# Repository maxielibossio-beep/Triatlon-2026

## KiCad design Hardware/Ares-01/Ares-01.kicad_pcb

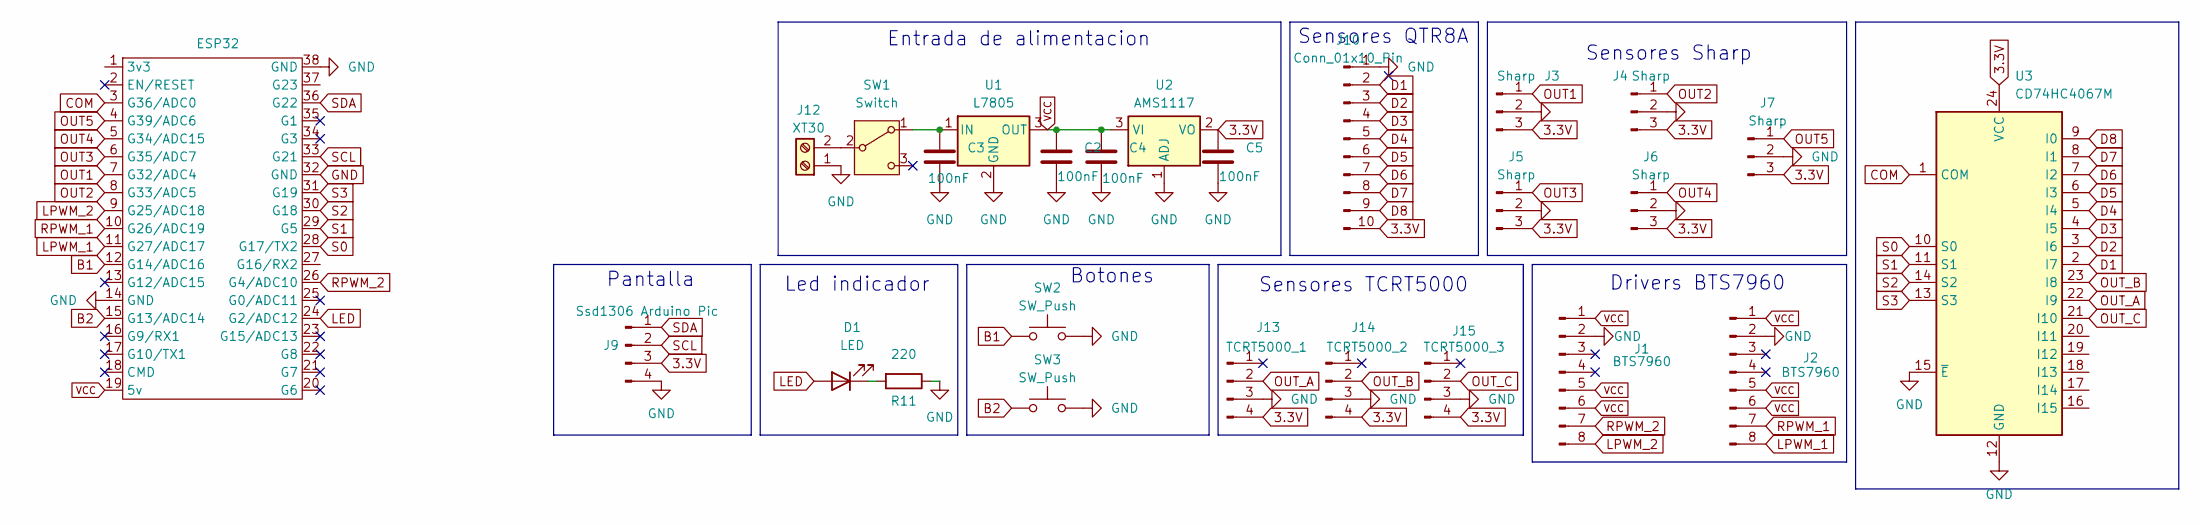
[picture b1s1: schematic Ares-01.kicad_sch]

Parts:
C2, C3, C4, C5: 100nF; C_0805_2012Metric
D1: LED; JST_EH_B2B-EH-A_1x02_P2.50mm_Vertical
ESP32: Nodemcu_ESP32S_38pin
J1, J2: BTS7960; IDC-Header_2x04_P2.54mm_Vertical
J3, J4, J5, J6, J7: Sharp; JST_XH_B3B-XH-A_1x03_P2.50mm_Vertical
J9: Ssd1306 Arduino Pic; JST_XH_B4B-XH-A_1x04_P2.50mm_Vertical
J10: Conn_01x10_Pin; JST_XH_B10B-XH-A_1x10_P2.50mm_Vertical
J12: XT30; XT30 connector
J13: TCRT5000_1; JST_XH_B4B-XH-A_1x04_P2.50mm_Vertical
J14: TCRT5000_2; JST_XH_B4B-XH-A_1x04_P2.50mm_Vertical
J15: TCRT5000_3; JST_XH_B4B-XH-A_1x04_P2.50mm_Vertical
R11: 220; R_0805_2012Metric
SW1: Switch; SW_SPDT_TH_Vertical
SW2, SW3: SW_Push; PUSH_SWITCH_THT
U1: L7805; TO-263-3_TabPin2
U2: AMS1117; SOT-223-3_TabPin2
U3: CD74HC4067M; CD74HC4067_module

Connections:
3.3V: C5.1, J3.3, J4.3, J5.3, J6.3, J7.3, J9.3, J10.10, J13.4, J14.4, J15.4, U2.2 (VO), U3.24 (VCC)
B1: ESP32.12 (G14/ADC16), SW2.1
B2: ESP32.15 (G13/ADC14), SW3.1
COM: ESP32.3 (G36/ADC0), U3.1 (COM)
D1: J10.2, U3.2 (I7)
D2: J10.3, U3.3 (I6)
D3: J10.4, U3.4 (I5)
D4: J10.5, U3.5 (I4)
D5: J10.6, U3.6 (I3)
D6: J10.7, U3.7 (I2)
D7: J10.8, U3.8 (I1)
D8: J10.9, U3.9 (I0)
GND: C2.2, C3.2, C4.2, C5.2, ESP32.14 (GND), ESP32.32 (GND), ESP32.38 (GND), J1.2, J2.2, J3.2, J4.2, J5.2, J6.2, J7.2, J9.4, J10.1, J12.1, J13.3, J14.3, J15.3, R11.1, SW2.2, SW3.2, U1.2 (GND), U2.1 (ADJ), U3.12 (GND), U3.15 (~E)
LED: D1.2 (A), ESP32.24 (G2/ADC12)
LPWM_1: ESP32.11 (G27/ADC17), J2.8
LPWM_2: ESP32.9 (G25/ADC18), J1.8
unnamed: D1.1 (K), R11.2
unnamed: J12.2, SW1.2 (B)
unnamed: C3.1, SW1.1 (A), U1.1 (IN)
OUT1: ESP32.7 (G32/ADC4), J3.1
OUT2: ESP32.8 (G33/ADC5), J4.1
OUT3: ESP32.6 (G35/ADC7), J5.1
OUT4: ESP32.5 (G34/ADC15), J6.1
OUT5: ESP32.4 (G39/ADC6), J7.1
OUT_A: J13.2, U3.22 (I9)
OUT_B: J14.2, U3.23 (I8)
OUT_C: J15.2, U3.21 (I10)
RPWM_1: ESP32.10 (G26/ADC19), J2.7
RPWM_2: ESP32.26 (G4/ADC10), J1.7
S0: ESP32.28 (G17/TX2), U3.10 (S0)
S1: ESP32.29 (G5), U3.11 (S1)
S2: ESP32.30 (G18), U3.14 (S2)
S3: ESP32.31 (G19), U3.13 (S3)
SCL: ESP32.33 (G21), J9.2
SDA: ESP32.36 (G22), J9.1
VCC: C2.1, C4.1, ESP32.19 (5v), J1.1, J1.5, J1.6, J2.1, J2.5, J2.6, U1.3 (OUT), U2.3 (VI)

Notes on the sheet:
Entrada de alimentacion
Led indicador
Sensores QTR8A
Botones
Sensores TCRT5000
Pantalla
Sensores Sharp
Drivers BTS7960

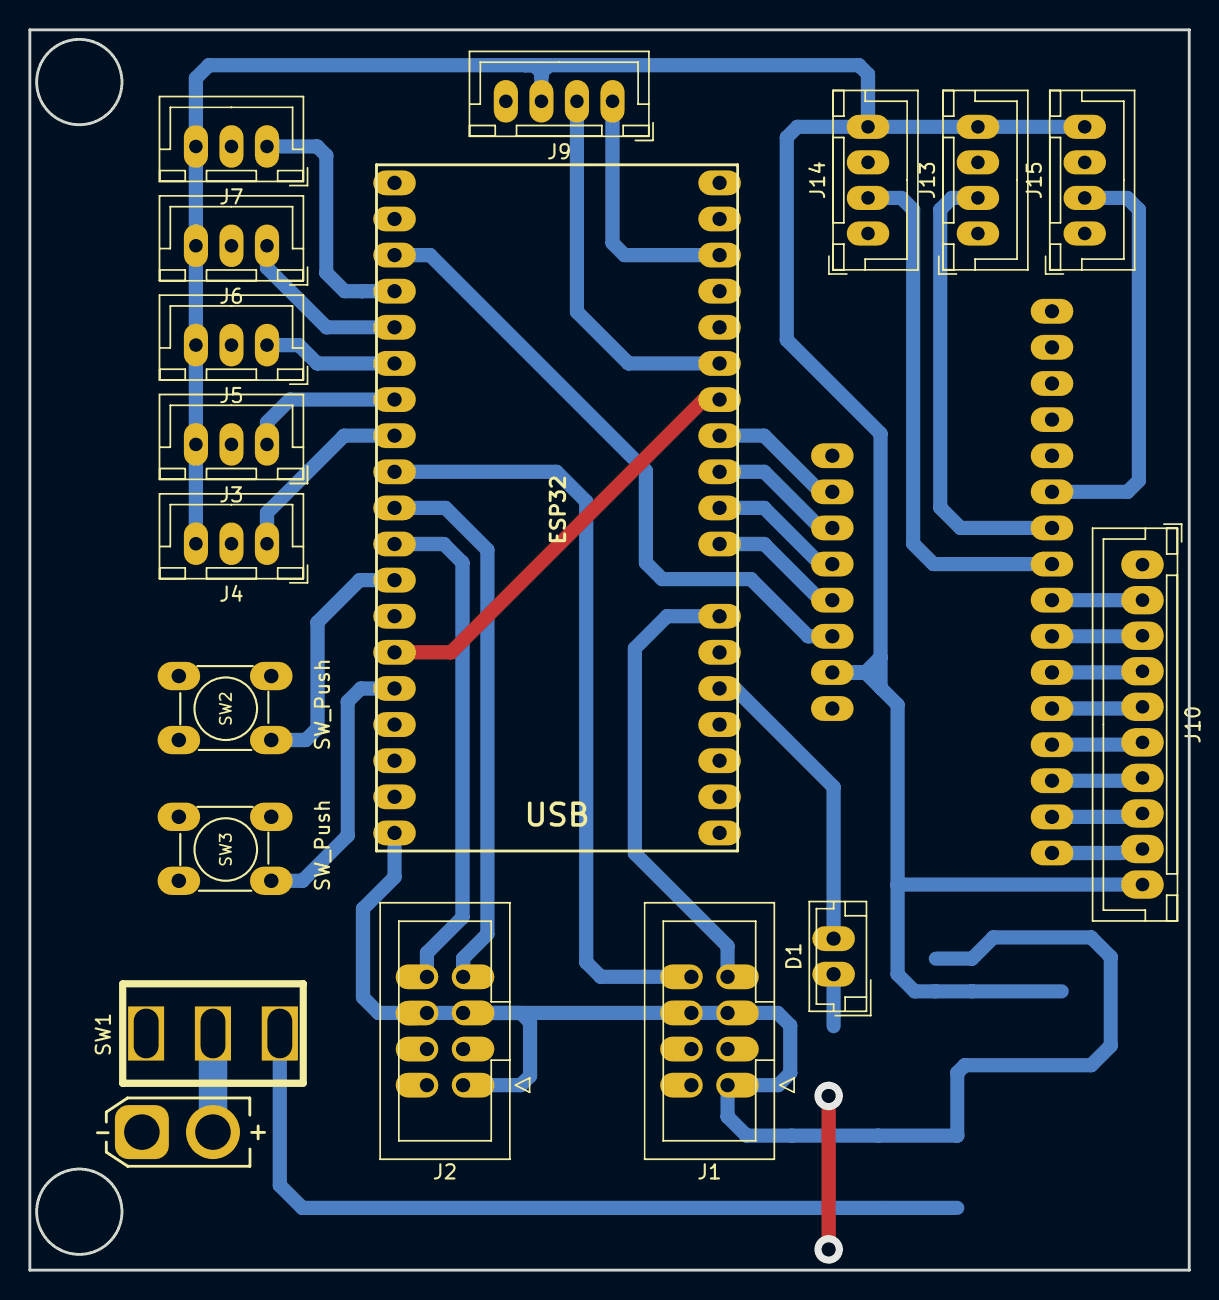
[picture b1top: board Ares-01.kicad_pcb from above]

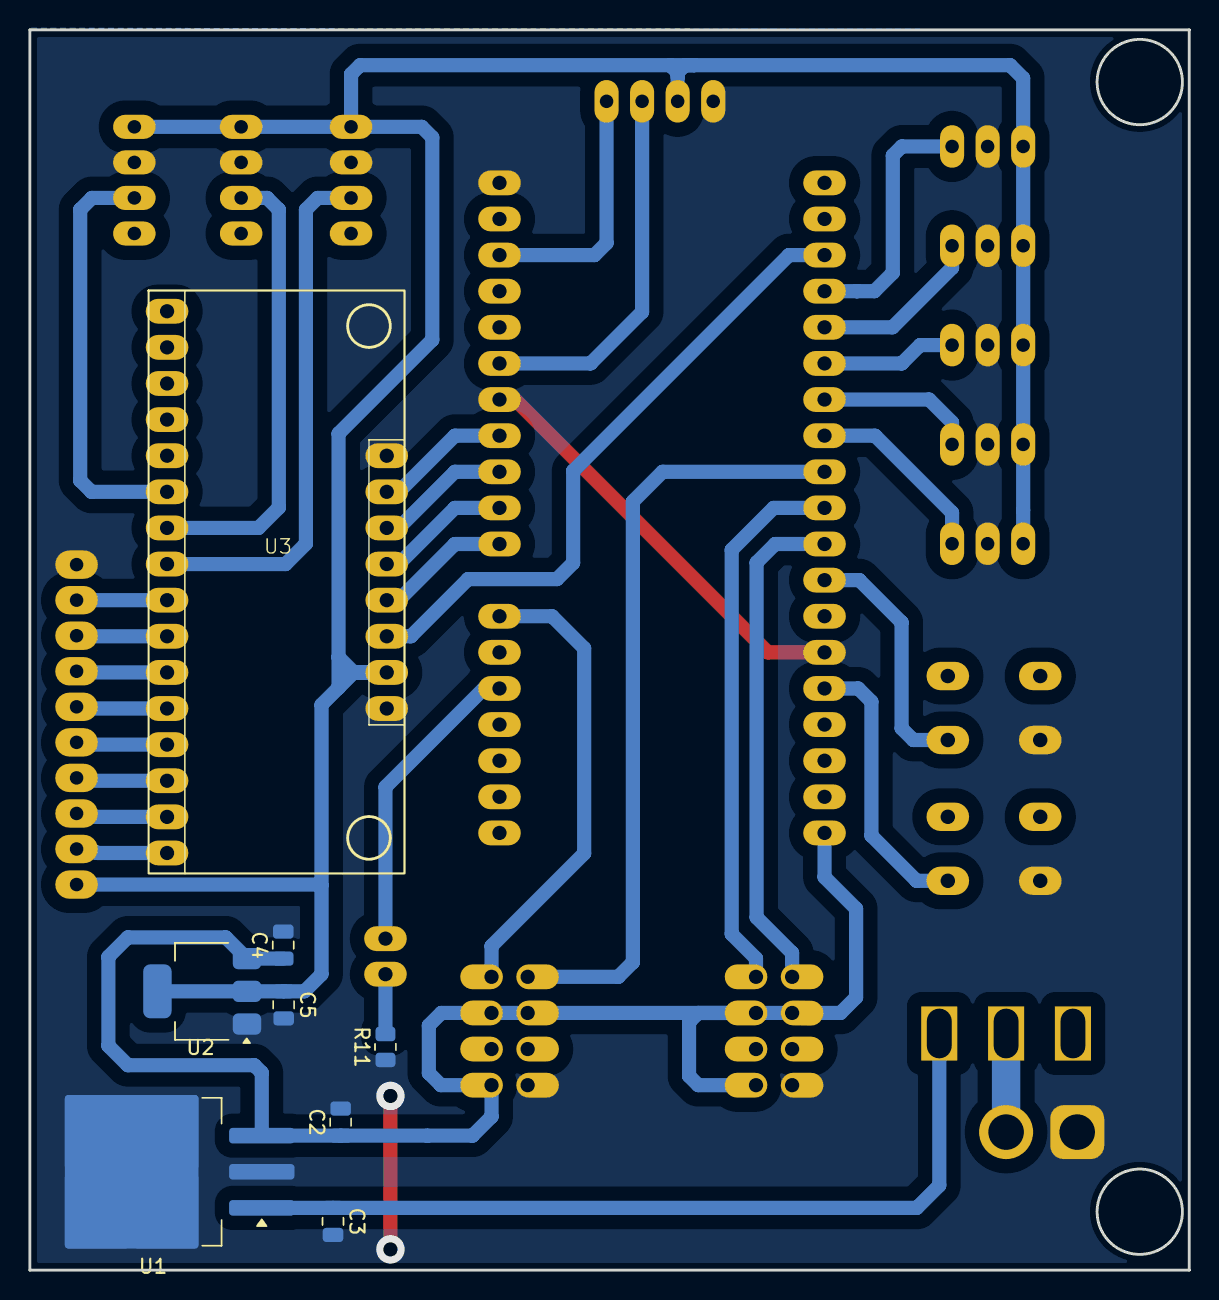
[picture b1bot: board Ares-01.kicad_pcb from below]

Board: 2 copper layers, 81.5 x 87.2 mm, 26 parts (8 on the bottom side), 36 nets.

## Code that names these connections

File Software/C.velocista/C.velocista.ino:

#include <BluetoothSerial.h>
#include <CD74HC4067.h>

#define RPWM_2 4
#define LPWM_2 25

#define RPWM_1 26
#define LPWM_1 27

#define pinBoton 13

CD74HC4067 my_mux(17, 5, 18, 19);

const int SIG = 36;

BluetoothSerial SerialBT;

const uint8_t SensorCount = 8;

uint16_t sensorValues[SensorCount];

int sensorMin[8];
int sensorMax[8];

float P;
float D;
float lastError = 0;

float Kp = 0.08;
float Kd = 0.60;

bool lastButton = HIGH;
int estado = 0;

void Bluetooth() {

  if (SerialBT.available()) {

    char dato = SerialBT.read();

    if (dato == 'A') Kp += 1;
    else if (dato == 'S') Kp += 0.1;

    else if (dato == 'D') Kp -= 1;
    else if (dato == 'F') Kp -= 0.1;

    else if (dato == 'G') Kd += 1;
    else if (dato == 'H') Kd += 0.1;

    else if (dato == 'J') Kd -= 1;
    else if (dato == 'K') Kd -= 0.1;

    SerialBT.print("Kp: ");
    SerialBT.print(Kp);
    SerialBT.print("  Kd: ");
    SerialBT.println(Kd);
  }
}

void leerSensores() {

  for (int i = 0; i < 8; i++) {

    my_mux.channel(i);

    delayMicroseconds(10);

    analogRead(SIG);

    delayMicroseconds(5);

    int suma = 0;

    for (int j = 0; j < 3; j++) {
      suma += analogRead(SIG);
    }

    sensorValues[i] = suma / 3;
  }
}

void normalizarSensores() {

  for (int i = 0; i < 8; i++) {
    if(SensorValues[i] > 800) SensorValues[i] = 1000;
 
  else{
    SensorValues[i] = 0;
 }

}

void mostrarSensores() {
  for (int i = 0; i < 8; i++) {

    Serial.print(sensorValues[i]);
    Serial.print('\t');
  }

  Serial.println();
}

void manejarBoton() {

  bool actual = digitalRead(pinBoton);

  if (lastButton == HIGH && actual == LOW) {

    delay(50);

    if (estado == 0) {

      calibrarSensores();

      estado = 1;

      Serial.println("Presiona nuevamente para iniciar");
    }

    else if (estado == 1) {

      estado = 2;

      Serial.println("Robot iniciado");
    }
  }

  lastButton = actual;
}

void ADELANTE(int velIzq, int velDer) {

  ledcWrite(RPWM_2, velIzq);
  ledcWrite(LPWM_2, 0);

  ledcWrite(RPWM_1, velDer);
  ledcWrite(LPWM_1, 0);
}


int pesos[8] = {
    -3500,
    -2500,
    -1500,
    -500,
     500,
     1500,
     2500,
     3500
  };

void PID_control() {

  leerSensores();

  normalizarSensores();

  long suma = 0;
  long total = 0;

  

  for (int i = 0; i < 8; i++) {

    suma += (long)sensorValues[i] * pesos[i];
    total += sensorValues[i];
  }

  if (total == 0) return;

  int position = suma / total;

  int error = position;

  P = error;
  D = error - lastError;

  lastError = error;

  int correction = (P * Kp) + (D * Kd);

  int baseSpeed = 150;

  int leftMotorSpeed = baseSpeed + correction;
  int rightMotorSpeed = baseSpeed - correction;

  leftMotorSpeed = constrain(leftMotorSpeed, 0, 220);
  rightMotorSpeed = constrain(rightMotorSpeed, 0, 220);

  ADELANTE(leftMotorSpeed, rightMotorSpeed);
}

void setup() {

  Serial.begin(115200);

  SerialBT.begin("ESP32_Seguidor");

  pinMode(pinBoton, INPUT_PULLUP);

  pinMode(SIG, INPUT);

  ledcAttach(RPWM_2, 5000, 8);
  ledcAttach(LPWM_2, 5000, 8);

  ledcAttach(RPWM_1, 5000, 8);
  ledcAttach(LPWM_1, 5000, 8);

  Serial.println("Listo para calibrar");
}

void loop() {
  Bluetooth();
  manejarBoton();

  if (estado == 2) {

    PID_control();
    mostrarSensores();
  }
}

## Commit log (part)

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2026-03-17 Mi primer commit
2026-03-17 Se crearon las carpetas del triatlon
2026-04-13 maia
2026-04-13 actualizacion Hardware
2026-04-29 se actualizo Hardware y Librerias
2026-05-03 Actualizacion de huellas
2026-05-06 primer version del pcb
2026-05-11 primera version del pcb,2
2026-05-11 Version 2.1 PCB
2026-05-20 version 3 del pcb
2026-06-28 Se subio las cosas faltantes
